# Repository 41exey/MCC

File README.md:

# Microclimate controller (MCC)

> Project based STM32F030K6T6

## Dependensies

- CMSIS

## Uses hardware

- TIM1 - sensor
- TIM3_CH3 PWM - backlight
- TIM14 - buttons
- TIM16 - time
- TIM17 - empty

- ADC1_IRQ - battery level

- Internal flash - storage settings

## Clone

> Clone this repo to your local machine using `git clone https://github.com/c1ewd/MCC`

## Features

> Device intended for measuring humidity and temperature. By deviation from specified range of temperature or humidity it send sound signal.
> Hardware design was making in Eagle CAD. Software was coding in IAR.
> Device is using digital humidity and temperature sensor AM2302. For sound signal using EFM-475. For graphical interface using Nokia 5110 display.

## Donations (Optional)

## License

- **[Apache 2.0 license](http://www.apache.org/licenses/LICENSE-2.0)**
- Copyright © 2020 <a href="https://teleg.run/c1ewd" target="_blank">c1ewd</a>.

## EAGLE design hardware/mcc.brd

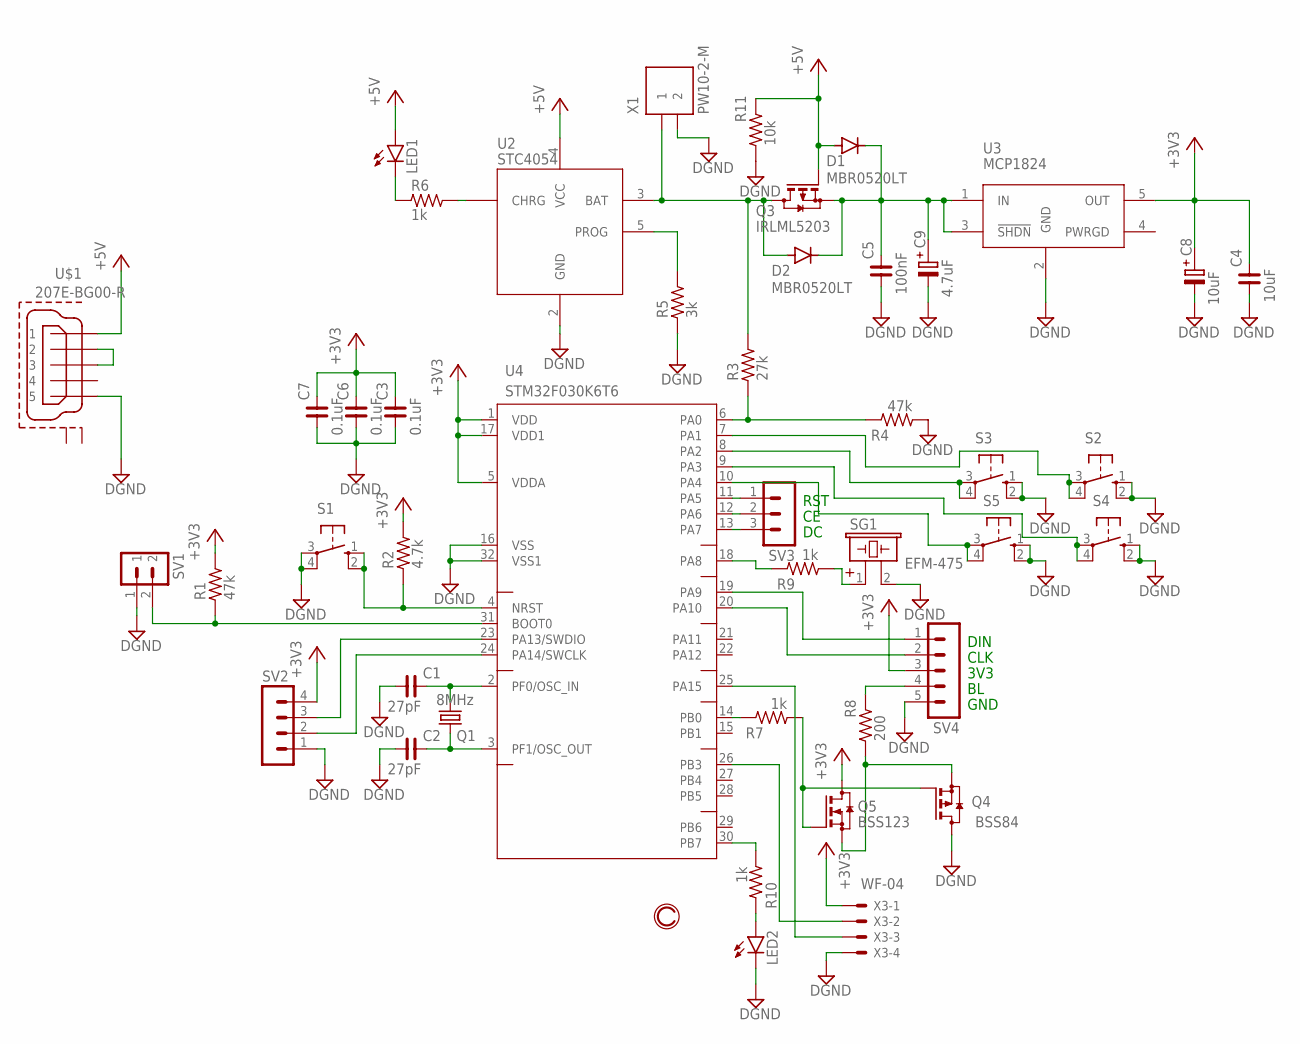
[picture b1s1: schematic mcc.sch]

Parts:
C1, C2: 27pF; C0805
C3, C6, C7: 0.1uF; C0805
C4: 10uF; C1206
C5: 100nF; C0805
C8: 10uF; SV-C
C9: 4.7uF; SV-C
D1, D2: MBR0520LT; SOD123
LED1, LED2: LEDSML0805; SML0805
Q1: 8MHz; HC49UP
Q3: IRLML5203; SOT23
Q4: BSS84; SOT23
Q5: BSS123; SOT23
R1, R4: 47k; R0805
R2: 4.7k; R0805
R3: 27k; R0805
R5: 3k; R0805
R6, R7, R9, R10: 1k; R0805
R8: 200; R0805
R11: 10k; R0805
S1, S2, S3, S4, S5: 10-XX; B3F-10XX
SG1: EFM-475; EFM-472
SV1: MA02-1
SV2: MA04-1
SV3: MA03-1
SV4: MA05-1
U2: STC4054; SOT23-5L
U3: MCP1824; SOT23-5L
U4: STM32F030K6T6; LQFP-32
U$1: 207E-BG00-R
X1: PW10-2-M; MKS1852-6-0-202
X3: WF-04; 22-23-2041

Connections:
+3V3: C3.2, C4.2, C6.2, C7.2, C8.+, Q5.3 (D), R1.2, R2.2, SV2.4, SV4.3, U3.5 (OUT), U4.1 (VDD), U4.5 (VDDA), U4.17 (VDD1), X3.1
BAT: D2.A, Q3.3 (D), R3.2, U2.3 (BAT), X1.1
BL: R7.2, U4.14 (PB0)
BOOT0: R1.1, SV1.2, U4.31 (BOOT0)
BUZZER: R9.2, U4.18 (PA8)
CE: SV3.2, U4.12 (PA6)
CHRG: R6.2, U2.1 (CHRG)
CLK: SV4.2, U4.20 (PA10)
DATA: U4.26 (PB3), X3.2
DC: SV3.3, U4.13 (PA7)
DGND: C1.1, C2.1, C3.1, C4.1, C5.1, C6.1, C7.1, C8.-, C9.-, LED2.C, Q4.3 (D), R4.1, R5.1, R11.1, S1.3, S1.4 (P1), S2.1 (S), S2.2 (S1), S3.1 (S), S3.2 (S1), S4.1 (S), S4.2 (S1), S5.1 (S), S5.2 (S1), SG1.2, SV1.1, SV2.1, SV4.5, U2.2 (GND), U3.2 (GND), U4.16 (VSS), U4.32 (VSS1), U$1.P$5 (5), X1.2, X3.4
DIN: SV4.1, U4.19 (PA9)
DIV_BAT: R3.1, R4.2, U4.6 (PA0)
LED2: R10.1, U4.30 (PB7)
unnamed: C5.2, C9.+, D1.C, D2.C, Q3.2 (S), U3.1 (IN), U3.3 (!SHDN)
unnamed: U$1.P$2 (2), U$1.P$3 (3)
unnamed: R8.2, SV4.4
unnamed: U4.25 (PA15), X3.3
NRST: R2.1, S1.1 (S), S1.2 (S1), U4.4 (NRST)
PF0-OSC_IN: C1.2, Q1.1, U4.2 (PF0/OSC_IN)
PF1-OSC_OUT: C2.2, Q1.2, U4.3 (PF1/OSC_OUT)
PROG: R5.2, U2.5 (PROG)
RST: SV3.1, U4.11 (PA5)
R_BL: Q4.1 (G), Q5.1 (G), R7.1
R_BUZZER: R9.1, SG1.1
R_CHRG: LED1.C, R6.1
R_LED2: LED2.A, R10.2
S2: S2.3, S2.4 (P1), U4.7 (PA1)
S3: S3.3, S3.4 (P1), U4.8 (PA2)
S4: S4.3, S4.4 (P1), U4.9 (PA3)
S5: S5.3, S5.4 (P1), U4.10 (PA4)
SWCLK: SV2.2, U4.24 (PA14/SWCLK)
SWDIO: SV2.3, U4.23 (PA13/SWDIO)
VCC: D1.A, LED1.A, Q3.1 (G), R11.2, U2.4 (VCC), U$1.P$1 (1)
Е_BL: Q4.2 (S), Q5.2 (S), R8.1

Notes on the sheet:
RST
DIN
CLK
3V3
GND

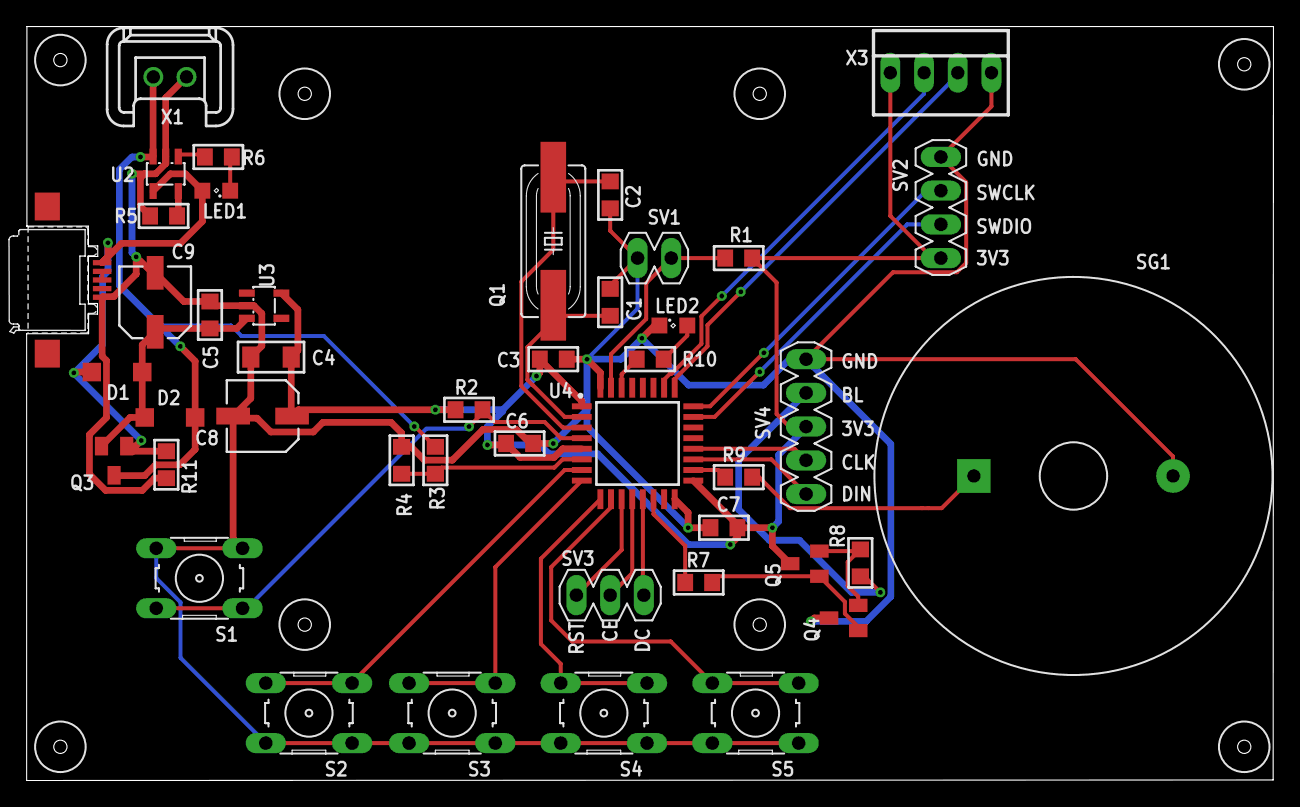
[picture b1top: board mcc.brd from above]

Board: 2 copper layers, 94.0 x 56.8 mm, 44 parts (0 on the bottom side), 35 nets.

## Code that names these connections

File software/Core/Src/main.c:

/*
 * Copyright 2020 c1ewd
 *
 * Licensed under the Apache License, Version 2.0 (the "License");
 * you may not use this file except in compliance with the License.
 * You may obtain a copy of the License at
 *
 *      http://www.apache.org/licenses/LICENSE-2.0
 *
 * Unless required by applicable law or agreed to in writing, software
 * distributed under the License is distributed on an "AS IS" BASIS,
 * WITHOUT WARRANTIES OR CONDITIONS OF ANY KIND, either express or implied.
 * See the License for the specific language governing permissions and
 * limitations under the License.
 */

#include "main.h"
#include "define.h"

#include "am2302.h"
#include "buttons.h"
#include "backlight.h"
#include "flash.h"
#include "string.h"
#include "sound.h"

/**
Test function indicates that MCU works
*/
void TIM17_IRQHandler(void)
{
//  LED_PORT->ODR ^= LED_ODR;
//  BUZZER_PORT->ODR ^= BUZZER_ODR;
    
  TIM17->SR &=~ TIM_SR_UIF;
}

/**
 * Program delay in milliseconds
 * @param ms delay in milliseconds
 */
void delay(uint32_t ms) {
  for(int i = 0; i < ms; i ++)
  {//48000000
    for(int j = 0; j < 48000; j ++)
    {
      __NOP();
    }
  }
}

int main(void)
{

  RCC->AHBENR |= RCC_AHBENR_GPIOBEN;
  // led
  GPIOB->MODER |= GPIO_MODER_MODER7_0;
  GPIOB->OTYPER &= ~GPIO_OTYPER_OT_7;
  GPIOB->OSPEEDR |= GPIO_OSPEEDER_OSPEEDR7;
  GPIOB->PUPDR |= GPIO_PUPDR_PUPDR7_0;
  
  RCC->AHBENR |= RCC_AHBENR_GPIOAEN;
  // Display
  // PA5
  GPIOA->MODER |= GPIO_MODER_MODER5_0;
  GPIOA->OTYPER &= ~GPIO_OTYPER_OT_5;
  GPIOA->OSPEEDR |= GPIO_OSPEEDER_OSPEEDR5;
  GPIOA->PUPDR &= ~GPIO_PUPDR_PUPDR5;
  // PA6
  GPIOA->MODER |= GPIO_MODER_MODER6_0;
  GPIOA->OTYPER &= ~GPIO_OTYPER_OT_6;
  GPIOA->OSPEEDR |= GPIO_OSPEEDER_OSPEEDR6;
  GPIOA->PUPDR &= ~GPIO_PUPDR_PUPDR6;   
  // PA7
  GPIOA->MODER |= GPIO_MODER_MODER7_0;
  GPIOA->OTYPER &= ~GPIO_OTYPER_OT_7;
  GPIOA->OSPEEDR |= GPIO_OSPEEDER_OSPEEDR7;
  GPIOA->PUPDR &= ~GPIO_PUPDR_PUPDR7;     
  // PA9
  GPIOA->MODER |= GPIO_MODER_MODER9_0;
  GPIOA->OTYPER &= ~GPIO_OTYPER_OT_9;
  GPIOA->OSPEEDR |= GPIO_OSPEEDER_OSPEEDR9;
  GPIOA->PUPDR &= ~GPIO_PUPDR_PUPDR9;
  // PA10
  GPIOA->MODER |= GPIO_MODER_MODER10_0;
  GPIOA->OTYPER &= ~GPIO_OTYPER_OT_10;
  GPIOA->OSPEEDR |= GPIO_OSPEEDER_OSPEEDR10;
  GPIOA->PUPDR &= ~GPIO_PUPDR_PUPDR10; 

  // PWM Display
  // TIM3_CH3
  // Configure PB0 for BL of LCD
//  GPIOB->MODER &= ~GPIO_MODER_MODER0;
  GPIOB->MODER |= GPIO_MODER_MODER0_1;
  GPIOB->OTYPER &= ~GPIO_OTYPER_OT_0;
  GPIOB->OSPEEDR |= GPIO_OSPEEDER_OSPEEDR0;
  GPIOB->PUPDR &= ~GPIO_PUPDR_PUPDR0;    
    
  // Enable PWM for LCD
  // Select AF1 on PB0 in AFRL for TIM3_CH3
  GPIOB->AFR[0] |= 0x01 << GPIO_AFRL_AFRL0_Pos;
  RCC->APB1ENR |= RCC_APB1ENR_TIM3EN;
  TIM3->PSC = 4800 - 1;
  TIM3->ARR = 100;
  TIM3->CCR3 = 100;
  TIM3->CCER |= TIM_CCER_CC3E;
  TIM3->BDTR |= TIM_BDTR_MOE;
  TIM3->CCMR2 = TIM_CCMR2_OC3M_2 | TIM_CCMR2_OC3M_1 | TIM_CCMR2_OC3PE;
  NVIC_SetPriority(TIM3_IRQn, 1);
  NVIC_EnableIRQ(TIM3_IRQn);
  TIM3->DIER = TIM_DIER_UIE;    
  TIM3->EGR |= TIM_EGR_UG;
    
  // time
  RCC->APB2ENR |= RCC_APB2ENR_TIM16EN;
  TIM16->PSC = 48000 - 1;
  TIM16->ARR = 500 - 1; // one per second, tested
  TIM16->CNT = 0;
  NVIC_SetPriority(TIM16_IRQn, 1);
  NVIC_EnableIRQ(TIM16_IRQn);
  TIM16->DIER = TIM_DIER_UIE;    
  TIM16->CR1 |= TIM_CR1_CEN | TIM_CR1_ARPE;
  
  // buzzer
  GPIOA->MODER |= GPIO_MODER_MODER8_0;
  GPIOA->OTYPER &= ~GPIO_OTYPER_OT_8;
  GPIOA->OSPEEDR |= GPIO_OSPEEDER_OSPEEDR8;
  GPIOA->PUPDR &= ~GPIO_PUPDR_PUPDR8;
  
  // TIM for tests
  /*
  RCC->APB2ENR |= RCC_APB2ENR_TIM17EN;
  TIM17->PSC = 48000 - 1;
  TIM17->ARR = 500;
  TIM17->CNT = 0;
  NVIC_SetPriority(TIM17_IRQn, 1);
  NVIC_EnableIRQ(TIM17_IRQn);
  TIM17->DIER = TIM_DIER_UIE;    
  TIM17->CR1 |= TIM_CR1_CEN | TIM_CR1_ARPE;
*/
  
  // PA0 ADC
  GPIOA->MODER |= GPIO_MODER_MODER0;
  // RCC of ADC
  RCC->APB2ENR |= RCC_APB2ENR_ADC1EN;
  RCC->CR2 |= RCC_CR2_HSI14ON;
  while((RCC->CR2 & RCC_CR2_HSI14RDY) == 0) {

  }

  ADC1->CFGR2 &= ~ADC_CFGR2_CKMODE;
  ADC1->CFGR2 |= ADC_CFGR2_CKMODE_1;
    
  ADC1->CFGR1 = 0;
    
  ADC1->CFGR1 |= ADC_CFGR1_CONT | ADC_CFGR1_SCANDIR;
  ADC1->CHSELR = ADC_CHSELR_CHSEL0;
  ADC1->SMPR |= ADC_SMPR_SMP_0 | ADC_SMPR_SMP_1 | ADC_SMPR_SMP_2;
  ADC1->IER = ADC_IER_EOCIE;
  NVIC_EnableIRQ(ADC1_COMP_IRQn);
  NVIC_SetPriority(ADC1_COMP_IRQn, 2);
    
  // Calibration
  // If enable
  if ((ADC1->CR & ADC_CR_ADEN) != 0) {
    ADC1->CR |= ADC_CR_ADDIS;
  }
  
  while((ADC1->CR & ADC_CR_ADEN) != 0) {

  }

  ADC1->CFGR1 &= ~ADC_CFGR1_DMAEN;
  ADC1->CR |= ADC_CR_ADCAL;
  while((ADC1->CR & ADC_CR_ADCAL) != 0) {
  }
    
  // ADC enable

  ADC1->CR |= ADC_CR_ADEN;
  while((ADC1->ISR & ADC_ISR_ADRDY) == 0) {
   
  }
    
  ADC1->CR |= ADC_CR_ADSTART;
  
  // AM2302
  // DATA pin is PB3
  GPIOB->MODER &= ~GPIO_MODER_MODER3;
  GPIOB->MODER |= GPIO_MODER_MODER3_0;
  GPIOB->OTYPER |= GPIO_OTYPER_OT_3;
  GPIOB->OSPEEDR |= GPIO_OSPEEDER_OSPEEDR3;
  GPIOB->PUPDR &= ~GPIO_PUPDR_PUPDR3;
    
  // AM2302 polling by TIM1
  RCC->APB2ENR |= RCC_APB2ENR_TIM1EN;
  // 240 / 48 000 000 = 1 / 200 000 = 0.000005 s = 0.005 ms = 5 us
  TIM1->PSC = 240 - 1;
  TIM1->ARR = 1;
  NVIC_SetPriority(TIM1_BRK_UP_TRG_COM_IRQn, 0);
  NVIC_EnableIRQ(TIM1_BRK_UP_TRG_COM_IRQn);
  TIM1->DIER = TIM_DIER_UIE;    
  TIM1->CR1 |= TIM_CR1_CEN | TIM_CR1_ARPE;
  TIM1->EGR |= TIM_EGR_UG;

  // Buttons
  // S2 - PA1
  // S3 - PA2
  // S4 - PA3
  // S5 - PA4
  // PA1
  GPIOA->MODER &= ~GPIO_MODER_MODER1; // Input mode
  GPIOA->OTYPER &= ~GPIO_OTYPER_OT_1; // Output push pull
  GPIOA->OSPEEDR |= GPIO_OSPEEDER_OSPEEDR1; // High speed
  GPIOA->PUPDR &= ~GPIO_PUPDR_PUPDR1;
  GPIOA->PUPDR |= GPIO_PUPDR_PUPDR1_0; // Pull-up
  // PA2
  GPIOA->MODER &= ~GPIO_MODER_MODER2; // Input mode
  GPIOA->OTYPER &= ~GPIO_OTYPER_OT_2; // Output push pull
  GPIOA->OSPEEDR |= GPIO_OSPEEDER_OSPEEDR2; // High speed
  GPIOA->PUPDR &= ~GPIO_PUPDR_PUPDR2;
  GPIOA->PUPDR |= GPIO_PUPDR_PUPDR2_0; // Pull-up    
  // PA3
  GPIOA->MODER &= ~GPIO_MODER_MODER3; // Input mode
  GPIOA->OTYPER &= ~GPIO_OTYPER_OT_3; // Output push pull
  GPIOA->OSPEEDR |= GPIO_OSPEEDER_OSPEEDR3; // High speed
  GPIOA->PUPDR &= ~GPIO_PUPDR_PUPDR3;
  GPIOA->PUPDR |= GPIO_PUPDR_PUPDR3_0; // Pull-up
  // PA4
  GPIOA->MODER &= ~GPIO_MODER_MODER4; // Input mode
  GPIOA->OTYPER &= ~GPIO_OTYPER_OT_4; // Output push pull
  GPIOA->OSPEEDR |= GPIO_OSPEEDER_OSPEEDR4; // High speed
  GPIOA->PUPDR &= ~GPIO_PUPDR_PUPDR4;
  GPIOA->PUPDR |= GPIO_PUPDR_PUPDR4_0; // Pull-up
    
  // Buttons polling by TIM14
  RCC->APB1ENR |= RCC_APB1ENR_TIM14EN;
  TIM14->PSC = 480 - 1;
  TIM14->ARR = 50;
  TIM14->CNT = 0;
  NVIC_SetPriority(TIM14_IRQn, 1);
  NVIC_EnableIRQ(TIM14_IRQn);
  TIM14->DIER = TIM_DIER_UIE;    
  TIM14->CR1 |= TIM_CR1_CEN | TIM_CR1_ARPE;
  
  lcd8544_init();
  lcd8544_clear();
  lcd8544_refresh(); 
  lcd8544_power_down();
  
  soundDelay = 10;
  
//  flashFirst();
  
  flashRead((unsigned char *)&settings, MEMORY_PAGE, sizeof(settings)); // page 28
//  memcpy((void *)&settingsBackup, (void *)&settings, sizeof(settings)); // wait for changes
  
  while(1) {

    sensorRead();
    show();
    delay(100);
    
  }
  
}

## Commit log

2022-09-25 Add project

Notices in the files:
parts and their libraries:
rc-master-smd: Copyright (C) 2007, Bob Starr
